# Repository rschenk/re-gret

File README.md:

# Re-gret Keyboard

The Re-gret is a 34 key remix of my [Egret](https://github.com/rschenk/egret) keyboard.

Featuring: 34 keys, Choc spacing, Choc v1 hot swappable, Seeed Xiao MCU, wireless compatible, RGB undeglow when plugged in, and a silicone gasket sandwich stackup.

Compared to the original Egret, besides having two thumb buttons per side, the Re-gret has a more angle between the halves, and the ring and pinky fingers have more stagger and more splay. It also has a Xiao MCU which is cheaper and cuter than a Nice Nano. Certainly a more re-fined re-mix that I have no re-grets about making.

## Build guide

Check the docs for a [PCB Build Guide](docs/pcb_build_guide.md) and [Case Build Guide](docs/case_build_guide.md).

## RGB Underglow

I powered the RGB underglow directly from the USB 5v, so it will automagically turn itself off when in wireless bluetooth mode. There's no need for ZMK's [External Power Control](https://zmk.dev/docs/behaviors/power#external-power-control) because you physically can't run the LEDs from battery power even if you wanted to. There's a [clever trick](https://hackaday.com/2017/01/20/cheating-at-5v-ws2812-control-to-use-a-3-3v-data-line/) using a diode that allows the 5v LEDs to be controlled by the Xiao's 3.3v logic.

## Firmware

### ZMK

I've published the firmware for Re-gret as a ZMK module: [rschenk/zmk-keyboard-re-gret](https://github.com/rschenk/zmk-keyboard-re-gret), which is (probably?) the preferred method for adding the keyboard in ZMK.

If you don't use modules, or prefer the old school way, then copy the contents of `firmware/zmk/config/boards/shields/regret/` into `[your-zmk-config]/config/boards/shields/regret/`

Be advised that right now the underglow only works on the XIAO nRF52840 board, and does not work on the XIAO RP2040 (although it [might in the future](https://github.com/zmkfirmware/zmk/issues/1085)). The original XIAO SAMD21 should work but I haven't tested it.

| Board                 | Chip     | USB Wired          | Bluetooth Wireless | RGB Underglow      | Comments                                                     |
| --------------------- | -------- | ------------------ | ------------------ | ------------------ | ------------------------------------------------------------ |
| XIAO                  | SAMD21   | :white_check_mark: | :x:                | :x:                | Should work but untested                                     |
| XIAO BLE              | nRF52840 | :white_check_mark: | :white_check_mark: | :white_check_mark: |                                                              |
| XIAO RP2040           | RP2040   | :white_check_mark: | :x:                | :x: for now        | Underglow [maybe someday](https://github.com/zmkfirmware/zmk/issues/1085) |

### QMK

Copy the contents of `firmware/qmk/keyboards/re_gret` into `[your_qmk_firmware]/keyboards/re_gret`, since I have not put the Re-gret firmware into the official QMK repo.

Only the XIAO RP2040 is supported. The Adafruit QT Py RP2040 might possibly work but I don't think the reset button will function.

| Board                 | Chip     | USB Wired          | RGB Underglow      | Comments                                                     |
| --------------------- | -------- | ------------------ | ------------------ | ------------------------------------------------------------ |
| XIAO RP2040           | RP2040   | :white_check_mark: | :white_check_mark: |  |

## Related

* I cribbed the Xiao footprint, pogo pin idea, and battery from the [revxlp](https://gitlab.com/lpgalaxy/revxlp)
* I based the QMK shift register matrix code on [Sadek's](https://github.com/sadekbaroudi/qmk_firmware)
* My original 36 key [Egret](https://github.com/rschenk/egret) was the starting point

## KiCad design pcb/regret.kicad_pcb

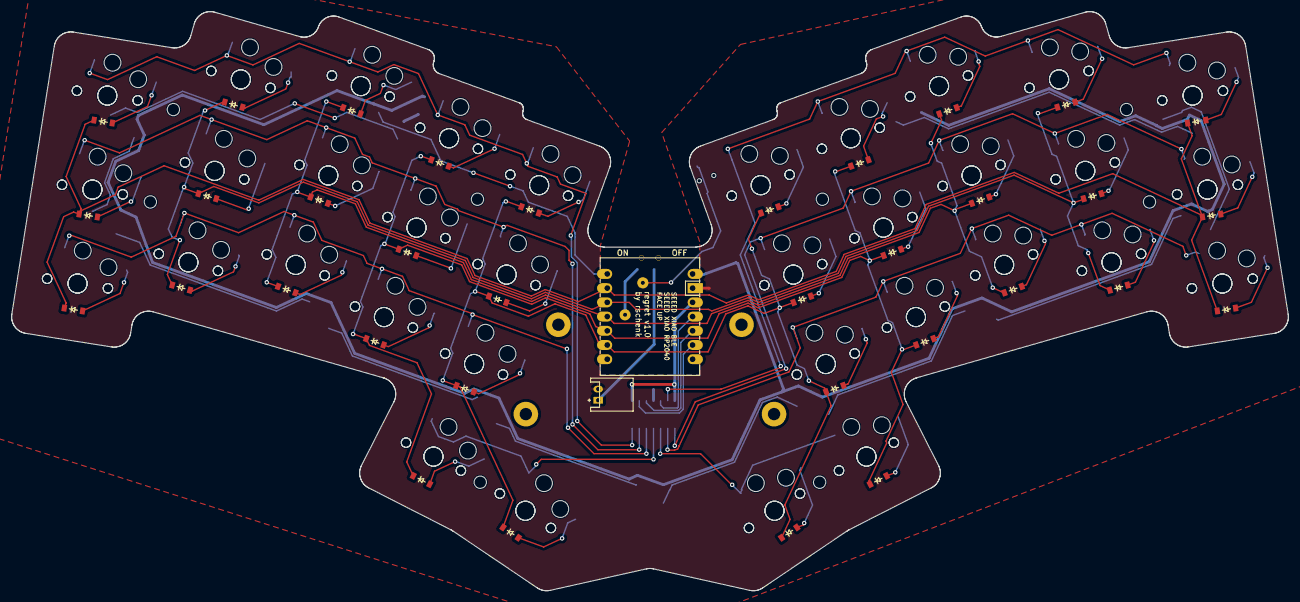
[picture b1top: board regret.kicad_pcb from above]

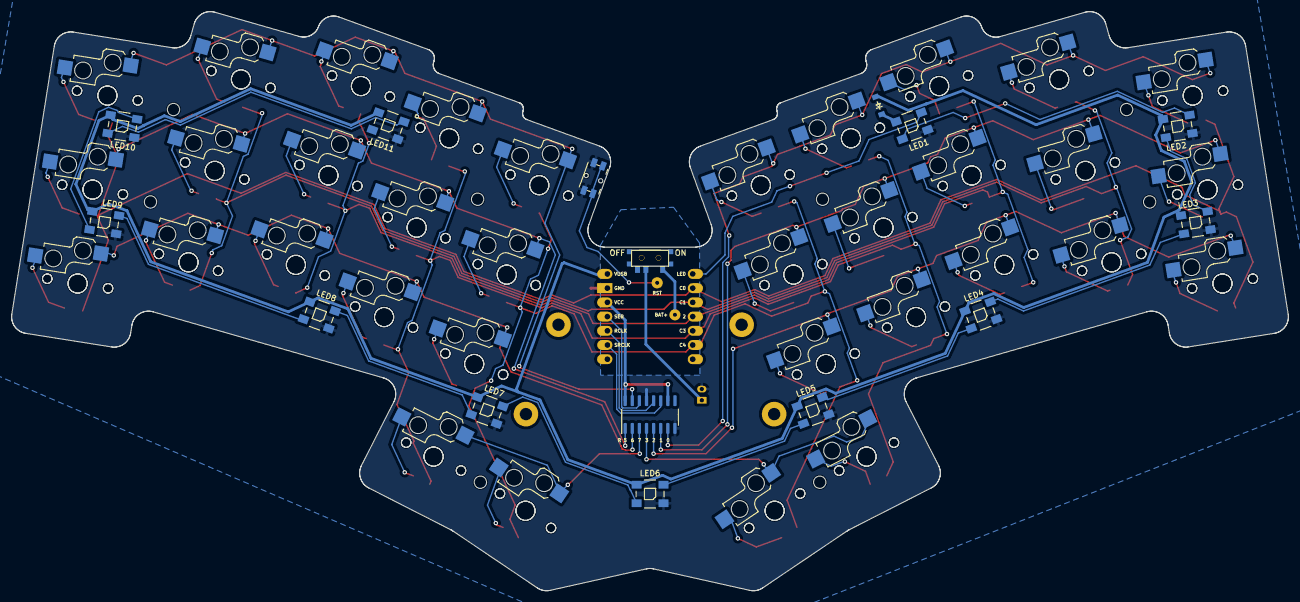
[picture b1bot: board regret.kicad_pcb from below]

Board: 2 copper layers, 228.1 x 103.5 mm, 131 parts (13 on the bottom side), 68 nets.

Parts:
19.051: 74HC595; SOIC-16_3.9x9.9mm_P1.27mm
B1: Panasonic_EVQPUL_EVQPUC
D1, D2, D3, D4, D5, D6, D7, D8, D9, D10, D11, D12, D13, D14, D15, D16, D17, D18, D19, D20, D21, D22, D23, D24, D25, D26, D27, D28, D29, D30, D31, D32, D33, D34, D35: ComboDiode
JST1: JST_PH_S2B-PH-K_02x2.00mm_Angled
LED1, LED2, LED3, LED4, LED5, LED6, LED7, LED8, LED9, LED10, LED11: VAL**; WS2812B
MCU1: xiao-ble
PAD1, PAD2, PAD3, PAD4: MountingHole_2.2mm_M2_Pad
PAD5, PAD6, PAD7, PAD8, PAD9, PAD10, PAD11, PAD12: MountingHole_2.2mm_M2
S1, S2, S3, S4, S5, S6, S7, S8, S9, S10, S11, S12, S13, S14, S15, S16, S17, S18, S19, S20, S21, S22, S23, S24, S25, S26, S27, S28, S29, S30, S31, S32, S33, S34: PG1350
SB1, SB2, SB3, SB4, SB5, SB6, SB7, SB8, SB9, SB10, SB11, SB12, SB13, SB14, SB15, SB16, SB17, SB18, SB19, SB20, SB21, SB22, SB23, SB24, SB25, SB26, SB27, SB28, SB29, SB30, SB31, SB32, SB33, SB34: ChocBonusGoodies
T1: SPDT_C128955

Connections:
BAT+: MCU1.19, T1.1
BAT_POS: JST1.1, T1.2
C0: D1.1, D2.1, D3.1, D16.1, D17.1, D18.1, MCU1.2
C1: D4.1, D5.1, D6.1, D19.1, D20.1, D21.1, MCU1.3
C2: D7.1, D8.1, D9.1, D22.1, D23.1, D24.1, MCU1.4
C3: D10.1, D11.1, D12.1, D25.1, D26.1, D27.1, D31.1, D33.1, MCU1.5
C4: D13.1, D14.1, D15.1, D28.1, D29.1, D30.1, D32.1, D34.1, MCU1.6
GND: 19.051.8, 19.051.13, B1.2, JST1.2, LED1.3, LED2.3, LED3.3, LED4.3, LED5.3, LED6.3, LED7.3, LED8.3, LED9.3, LED10.3, LED11.3, MCU1.13
L2: LED1.2, LED2.4
L3: LED2.2, LED3.4
L4: LED3.2, LED4.4
L5: LED4.2, LED5.4
L6: LED5.2, LED6.4
L7: LED6.2, LED7.4
L8: LED7.2, LED8.4
L9: LED8.2, LED9.4
L10: LED9.2, LED10.4
L11: LED10.2, LED11.4
LED: LED1.4, MCU1.1
R0: 19.051.7, S3.1, S6.1, S9.1, S12.1, S15.1
R1: 19.051.6, S2.1, S5.1, S8.1, S11.1, S14.1
R2: 19.051.5, S1.1, S4.1, S7.1, S10.1, S13.1
R3: 19.051.4, S31.1, S32.1
R4: 19.051.15, S18.1, S21.1, S24.1, S27.1, S30.1
R5: 19.051.1, S17.1, S20.1, S23.1, S26.1, S29.1
R6: 19.051.2, S16.1, S19.1, S22.1, S25.1, S28.1
R7: 19.051.3, S33.1, S34.1
RCLK: 19.051.12, MCU1.10
RST: B1.1, MCU1.17
SER: 19.051.14, MCU1.11
SRCLK: 19.051.11, MCU1.9
VCC: 19.051.10, 19.051.16, MCU1.12
VUSB: D35.2, LED2.1, LED3.1, LED4.1, LED5.1, LED6.1, LED7.1, LED8.1, LED9.1, LED10.1, LED11.1, MCU1.14
home_thumb: D31.2, S31.2
index_bottom: D10.2, S10.2
index_home: D11.2, S11.2
index_top: D12.2, S12.2
inner_bottom: D13.2, S13.2
inner_home: D14.2, S14.2
inner_top: D15.2, S15.2
led_1_v: D35.1, LED1.1
middle_bottom: D7.2, S7.2
middle_home: D8.2, S8.2
middle_top: D9.2, S9.2
mirror_home_thumb: D33.2, S33.2
mirror_index_bottom: D25.2, S25.2
mirror_index_home: D26.2, S26.2
mirror_index_top: D27.2, S27.2
mirror_inner_bottom: D28.2, S28.2
mirror_inner_home: D29.2, S29.2
mirror_inner_top: D30.2, S30.2
mirror_middle_bottom: D22.2, S22.2
mirror_middle_home: D23.2, S23.2
mirror_middle_top: D24.2, S24.2
mirror_pinky_bottom: D16.2, S16.2
mirror_pinky_home: D17.2, S17.2
mirror_pinky_top: D18.2, S18.2
mirror_reachy_thumb: D34.2, S34.2
mirror_ring_bottom: D19.2, S19.2
mirror_ring_home: D20.2, S20.2
mirror_ring_top: D21.2, S21.2
pinky_bottom: D1.2, S1.2
pinky_home: D2.2, S2.2
pinky_top: D3.2, S3.2
reachy_thumb: D32.2, S32.2
ring_bottom: D4.2, S4.2
ring_home: D5.2, S5.2
ring_top: D6.2, S6.2

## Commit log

2023-06-15 Init
2023-06-16 footprint for sk6812-mini-e
2023-06-16 Change center_spread to keycap edges instead of center
2023-06-16 Embrace `mirror` for LED layout
2023-06-16 Hide mini-e LED ref
2023-06-16 Add sacrificial diode to LED1
2023-06-16 Change to mini-e leds for underglow
2024-06-19 v1.0.0
2024-06-22 Readme and build guide
2024-06-23 ZMK firmware
2024-06-26 QMK firmware
2024-07-31 Combos on default keymap for flashing and RBG
2024-10-24 SVG and DXF format case files
2025-04-23 Add link to ZMK module
